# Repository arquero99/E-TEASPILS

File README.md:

# TEASPILS
Teaching Environmental Awareness with Smart IoT Planters in Learning Spaces (TEASPILS)
Developed in Informatic Systems Engineering faculty (ETSISI), in the Politechnical University of Madrid (UPM)

## About the project
The TEASPILS project focuses on creating environmental awareness towards plants and greenery, educating young people and their teachers towards ecological learning spaces. Actions will promote and foster awareness of environmental issues in an educational context, e.g. the sustainable development goals (SDGs) of the UN Agenda 2030. Unlike the wider agenda of protecting natural habitats like rainforests, our approach aims to stimulate knowledge and appreciation of plants close to the people concerned, i.e. in urban indoor and outdoor environments. Especially, the effects of plants in classrooms, offices, homes and public spaces have hitherto been undervalued. The project will target young people from an early age onwards, with students from primary, secondary and tertiary level to learn about potted plants in their immediate vicinity. With this promotion of plant appreciation at a young age, the project intends to lay the foundation of much wider protective attitudes of natural and artifical flora (and fauna). Therefore, it is considered to enhance thinking about the positive effects plants have on the climate and environmental well-being of our planet.
 
With a technology-enhanced approach using sensors and visualisations, children will not only learn basic facts about plants, but also about care and responsibility towards them. We use the cascading approach via primary and secondary school teachers, educational leaders, lecturers and support staff to establish a wide-ranging plant supported school climate, as well as measuring and evaluating their impact on learning and social behaviours.

## 3D Printed Design
The device has been embedded into a 3D printed case, designed by Juan Luis Moreno, that looks like a small green house. This case can be nailed into a planter using it as a Spike, or placed in a plain surface.
Protects the electronic device against dust and water, and gives a friendly interface for the user.

## PCB
All the electronics components and peripheralls has been interconected using a printed circuit board. This gives more reliability and robustness to the design, and makes it compatible with masive production tecniques. In addition, JST connectors has been used as ports for interfacing with the diferent peripheralls of the system. These kind of connectors have a lock in one of the sides that both locks the connection and avoids a incorrect positioning of the connector.

## Dashboards
A graphication system has been developed using the Thingsboard interface. Each one of the users has a especific user that allows him to see the related dashboard.

## About Us
We are Juan Arquero and Juan Luis Moreno, computer engineering students at the Politechnical University of Madrid.

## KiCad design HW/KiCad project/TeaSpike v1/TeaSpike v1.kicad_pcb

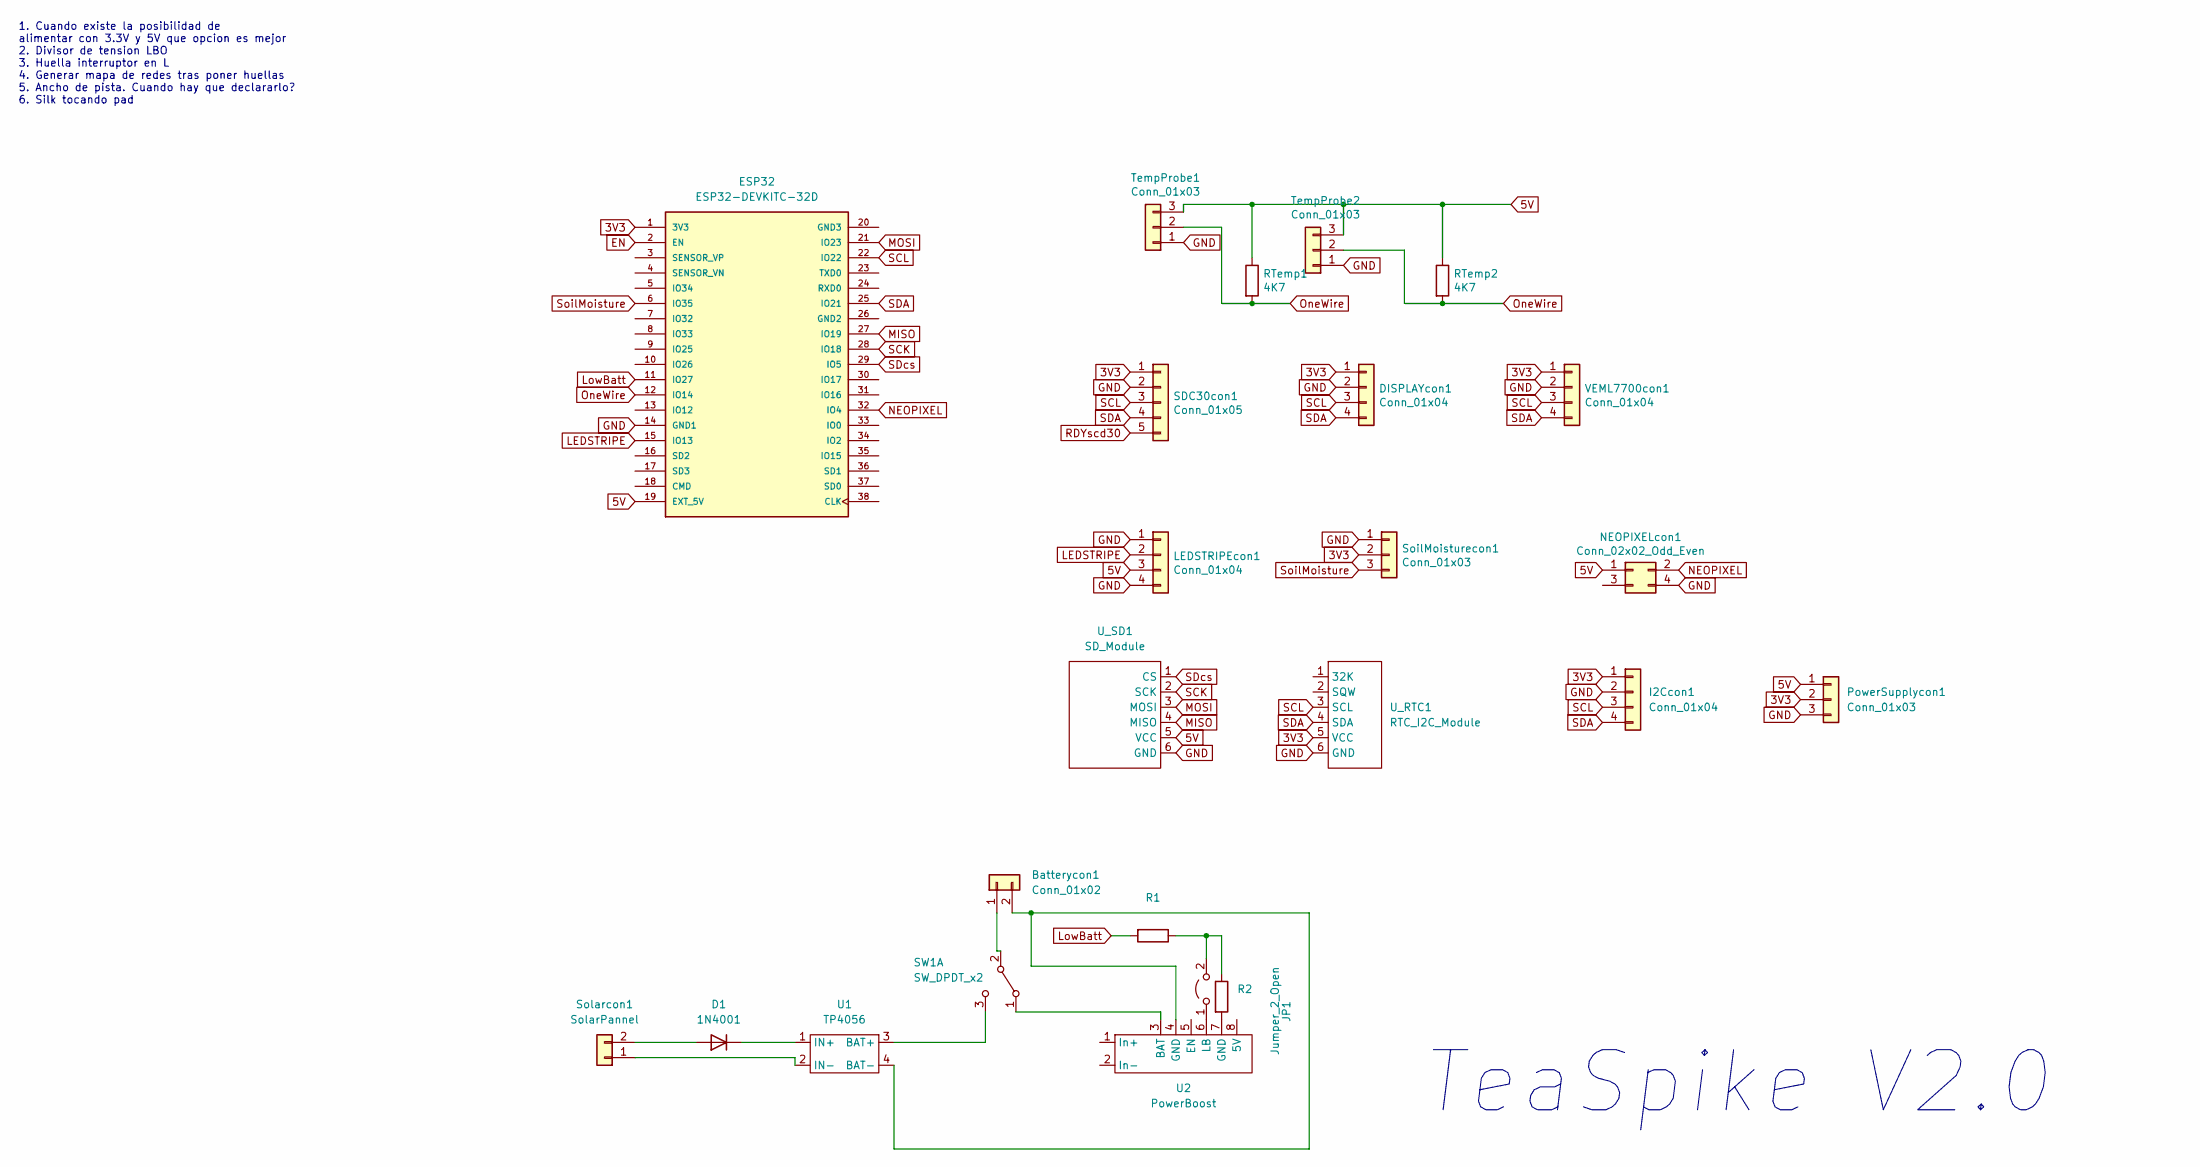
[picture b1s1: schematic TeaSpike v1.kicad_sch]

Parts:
Batterycon1: Conn_01x02; TerminalBlock_bornier-2_P5.08mm
D1: 1N4001; D_DO-41_SOD81_P10.16mm_Horizontal
DISPLAYcon1: Conn_01x04; JST_EH_B4B-EH-A_1x04_P2.50mm_Vertical
ESP32: ESP32-DEVKITC-32D; MODULE_ESP32-DEVKITC-32D; PARTREV 4
I2Ccon1: Conn_01x04; PinSocket_1x04_P2.54mm_Vertical
JP1: Jumper_2_Open; PinHeader_1x02_P2.54mm_Vertical
LEDSTRIPEcon1: Conn_01x04; JST_EH_B4B-EH-A_1x04_P2.50mm_Vertical
NEOPIXELcon1: Conn_02x02_Odd_Even; PinSocket_2x02_P2.54mm_Vertical
PowerSupplycon1: Conn_01x03; PinSocket_1x03_P2.54mm_Vertical
R1, R2: R_Axial_DIN0207_L6.3mm_D2.5mm_P7.62mm_Horizontal
RTemp1, RTemp2: 4K7; R_Axial_DIN0207_L6.3mm_D2.5mm_P7.62mm_Horizontal
SDC30con1: Conn_01x05; JST_EH_B5B-EH-A_1x05_P2.50mm_Vertical
SW1: SW_DPDT_x2; SW_CuK_JS202011AQN_DPDT_Angled
SoilMoisturecon1: Conn_01x03; PinHeader_1x03_P2.54mm_Vertical
Solarcon1: SolarPannel; TerminalBlock_bornier-2_P5.08mm
TempProbe1, TempProbe2: Conn_01x03; JST_EH_B3B-EH-A_1x03_P2.50mm_Vertical
U1: TP4056
U2: PowerBoost
U_RTC1: RTC_I2C_Module
U_SD1: SD_Module
VEML7700con1: Conn_01x04; JST_EH_B4B-EH-A_1x04_P2.50mm_Vertical

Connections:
3V3: DISPLAYcon1.1, ESP32.1 (3V3), I2Ccon1.1, PowerSupplycon1.2, SDC30con1.1, SoilMoisturecon1.2, U_RTC1.5 (VCC), VEML7700con1.1; also elsewhere on the board
5V: ESP32.19 (EXT_5V), LEDSTRIPEcon1.3, NEOPIXELcon1.1, PowerSupplycon1.1, RTemp1.1, RTemp2.1, TempProbe1.3, TempProbe2.3, U_SD1.5 (VCC)
EN: ESP32.2 (EN)
GND: DISPLAYcon1.2, ESP32.14 (GND1), I2Ccon1.2, LEDSTRIPEcon1.1, LEDSTRIPEcon1.4, NEOPIXELcon1.4, PowerSupplycon1.3, SDC30con1.2, SoilMoisturecon1.1, TempProbe1.1, TempProbe2.1, U_RTC1.6 (GND), U_SD1.6 (GND), VEML7700con1.2; also elsewhere on the board
LEDSTRIPE: ESP32.15 (IO13), LEDSTRIPEcon1.2
LowBatt: ESP32.11 (IO27), R1.2
MISO: ESP32.27 (IO19), U_SD1.4 (MISO)
MOSI: ESP32.21 (IO23), U_SD1.3 (MOSI)
NEOPIXEL: ESP32.32 (IO4), NEOPIXELcon1.2
unnamed 9: Batterycon1.1, SW1.2 (B); also elsewhere on the board
unnamed: Batterycon1.2, U1.4 (BAT-), U2.4 (GND)
unnamed: D1.1 (K), U1.1 (IN+)
unnamed: D1.2 (A), Solarcon1.2
unnamed: JP1.1 (A), U2.6 (LB)
unnamed: JP1.2 (B), R1.1, R2.1
unnamed: R2.2, U2.7 (GND)
unnamed 16: SW1.1 (A), U2.3 (BAT); also elsewhere on the board
unnamed 17: SW1.3 (C), U1.3 (BAT+); also elsewhere on the board
unnamed: Solarcon1.1, U1.2 (IN-)
OneWire: ESP32.12 (IO14), RTemp1.2, RTemp2.2, TempProbe1.2, TempProbe2.2
SCK: ESP32.28 (IO18), U_SD1.2 (SCK)
SCL: DISPLAYcon1.3, ESP32.22 (IO22), I2Ccon1.3, SDC30con1.3, U_RTC1.3 (SCL), VEML7700con1.3; also elsewhere on the board
SDA: DISPLAYcon1.4, ESP32.25 (IO21), I2Ccon1.4, SDC30con1.4, U_RTC1.4 (SDA), VEML7700con1.4; also elsewhere on the board
SDcs: ESP32.29 (IO5), U_SD1.1 (CS)
SoilMoisture: ESP32.6 (IO35), SoilMoisturecon1.3

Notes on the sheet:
TeaSpike V2.0
1. Cuando existe la posibilidad de alimentar con 3.3V y 5V que opcion es mejor 2. Divisor de tension LBO 3. Huella interruptor en L 4. Generar mapa de redes tras poner huellas 5. Ancho de pista. Cuando hay que declararlo? 6. Silk tocando pad

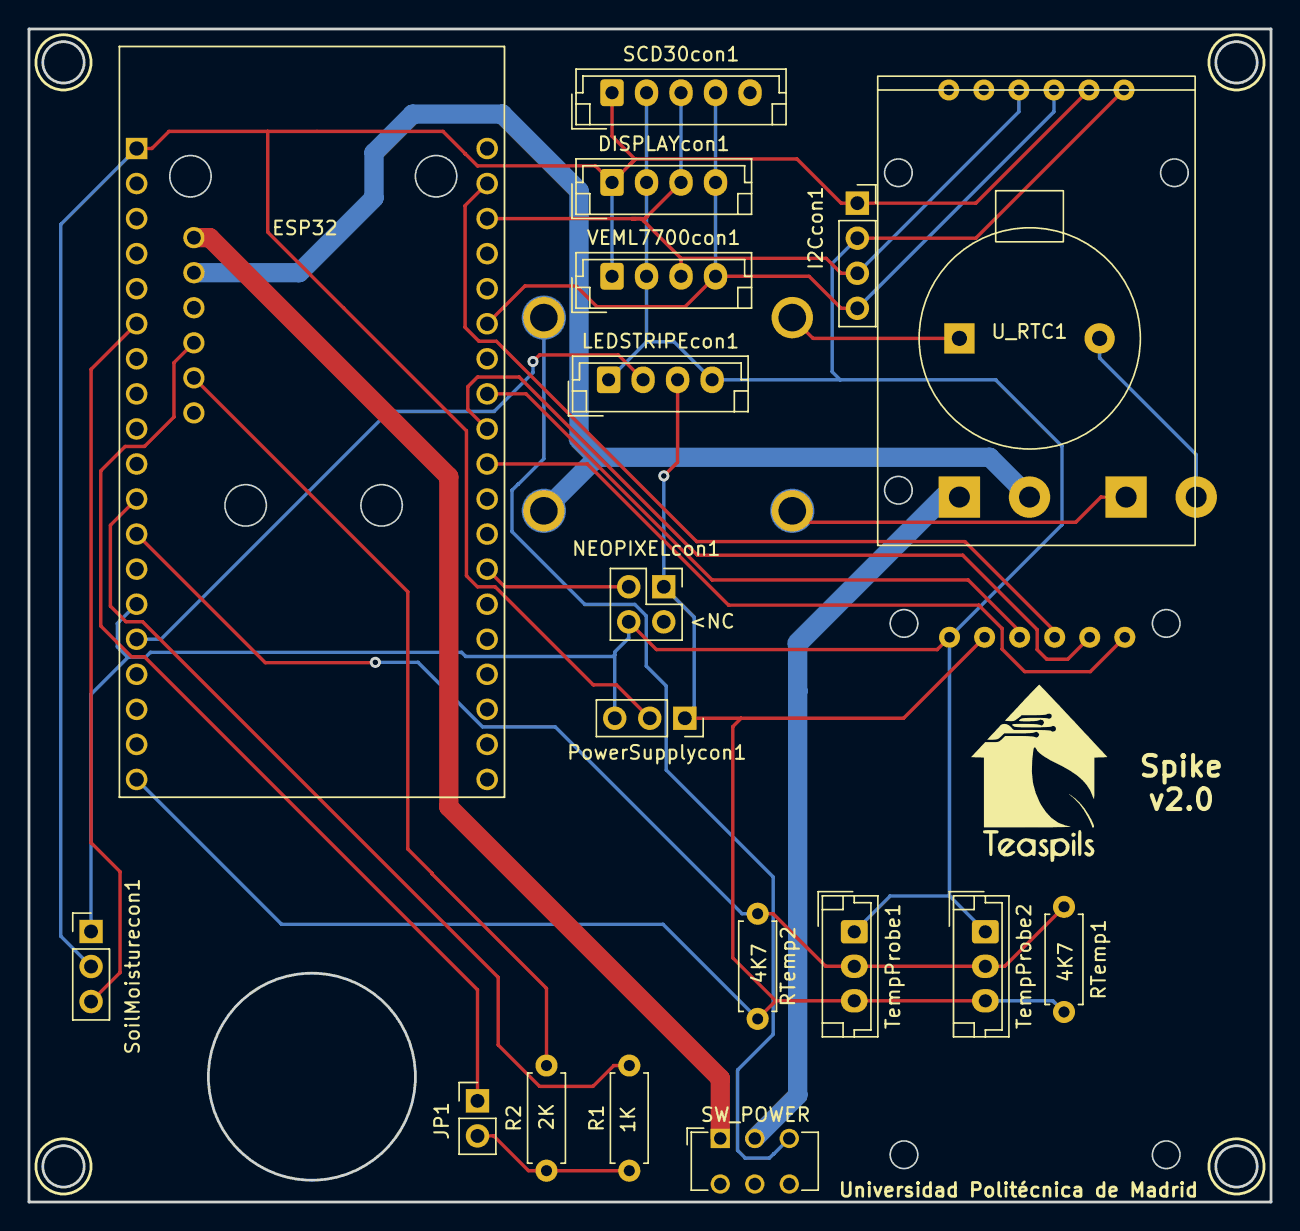
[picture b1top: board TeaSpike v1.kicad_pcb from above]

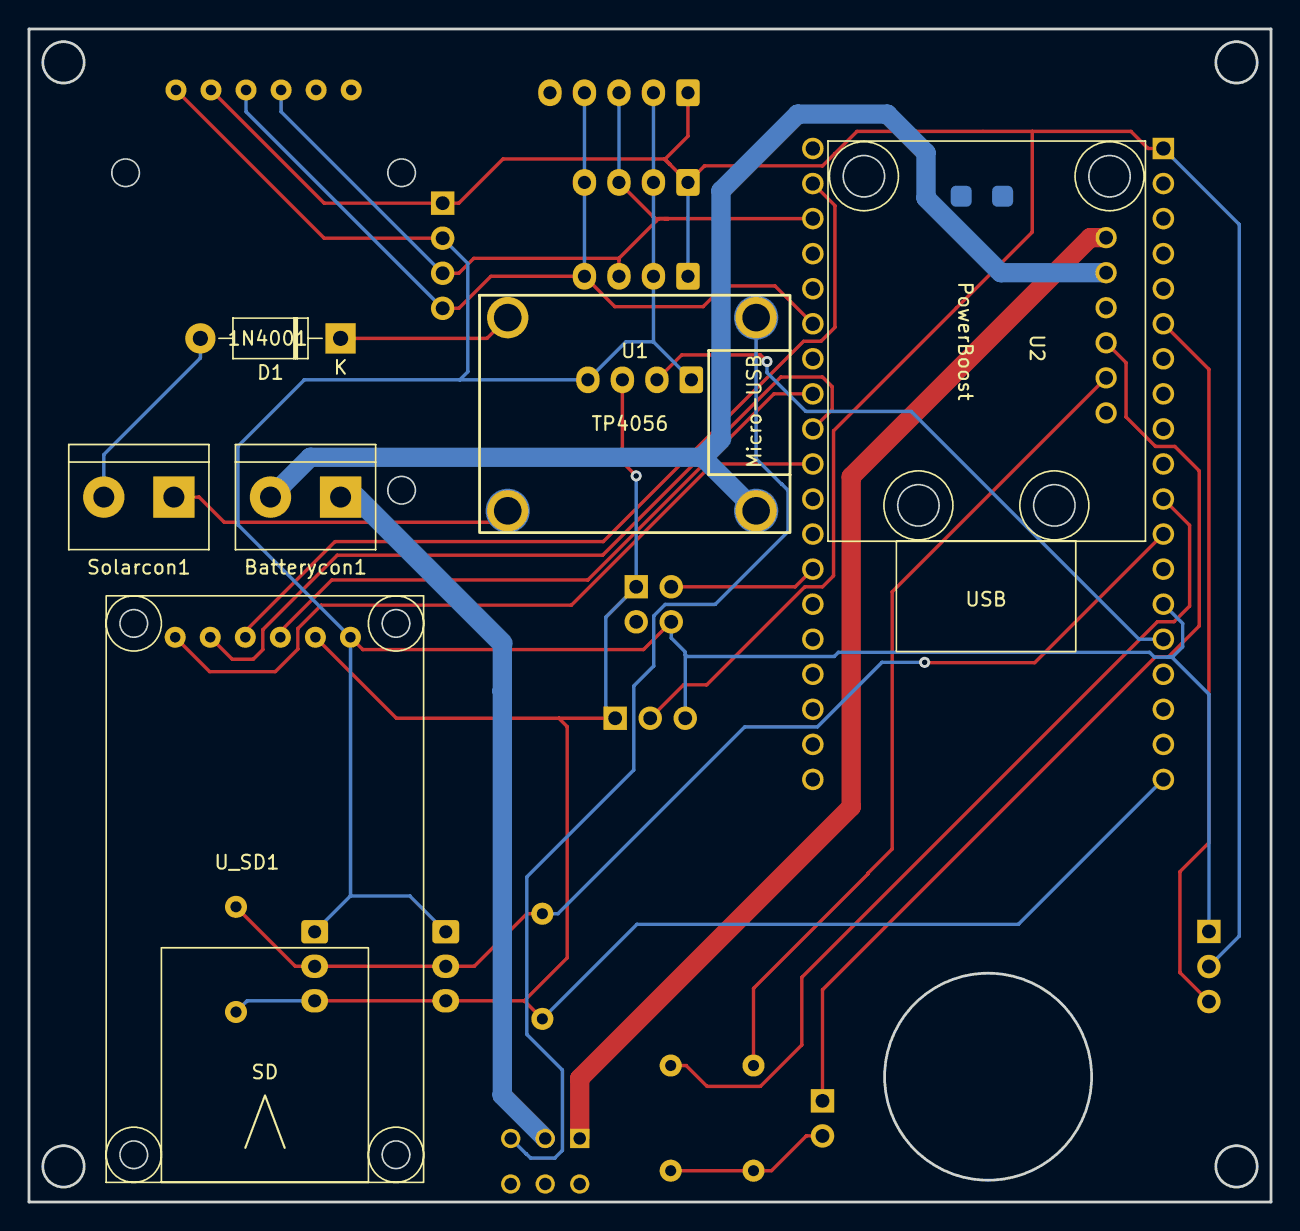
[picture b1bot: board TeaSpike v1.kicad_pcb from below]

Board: 2 copper layers, 90.0 x 85.0 mm, 24 parts (6 on the bottom side), 24 nets.

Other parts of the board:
SCD30con1: Conn_01x05; JST_EH_B5B-EH-A_1x05_P2.50mm_Vertical
SW_POWER: SW_DPDT_x2; SW_CuK_JS202011AQN_DPDT_Angled

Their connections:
3V3: SCD30con1.1; also elsewhere on the board
GND: SCD30con1.2; also elsewhere on the board
unnamed 9: SW_POWER.2 (B); also elsewhere on the board
unnamed 16: SW_POWER.1 (A); also elsewhere on the board
unnamed 17: SW_POWER.3 (C); also elsewhere on the board
SCL: SCD30con1.3; also elsewhere on the board
SDA: SCD30con1.4; also elsewhere on the board

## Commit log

2022-05-29 Updated gitignore file
2022-05-29 Updated gitignore for excluding credentials
2022-05-29 Updating filesystem to Viena congess
2022-05-29 Updated Readme. In progreess
2022-05-29 Updating readme 2
2022-06-05 Added 3D Model of PCB
2022-06-05 Added photos and updated README
2022-06-05 Family photo
2022-06-05 Updated README with full info
2022-09-12 updated gitignore
2022-09-12 Version 2.0
2022-09-12 Version 2.1
2022-10-02 Version 2.2
2022-11-17 Version 3
